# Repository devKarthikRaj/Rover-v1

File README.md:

# Rover-v1
<div align="center"></div><br>
<b>Rover v1 Documentation <br> 
Initial build completed on 21st January 2022.<br>
The inital build is a joystick controlled rover. <br>
Created for my own reference in the future and for any interested engineer wannabes (like myself) out there! <br> </b>

## Quick Reference
<b>Electrical</b> <br>
<i>Eagle PCBs</i> <br>
[Power Distribution Board](https://github.com/devKarthikRaj/Rover-v1/tree/master/Electrical/PCBs/Power%20Distribution%20Board/PDB%20v0) <br>
[Motor Driver](https://github.com/devKarthikRaj/Rover-v1/tree/master/Electrical/PCBs/Not%20in%20Use/Motor%20Driver/Rover%20MDrv%20v1) <br>
[Motor Controller](https://github.com/devKarthikRaj/Rover-v1/tree/master/Electrical/PCBs/Motor%20Controller/MCon%20v1) <br>
[Remote Control](https://github.com/devKarthikRaj/Rover-v1/tree/master/Electrical/PCBs/Remote%20Control/Rover%20Bt%20Remote) <br>

<i>Arduino Header Files</i> <br>
[Rover v1 Pin Configuration Header](https://github.com/devKarthikRaj/Rover-v1/tree/master/Electrical/Firmware/Arduino%20Libraries/roverV1) <br>

<i>Arduino Firmware</i> <br>
[Low Level Controller](https://github.com/devKarthikRaj/Rover-v1/tree/master/Electrical/Firmware/Low_Level_Controller_FW) <br>
[Motor Controller](https://github.com/devKarthikRaj/Rover-v1/tree/master/Electrical/Firmware/Motor_Controller_FW) <br>
[Remote Control](https://github.com/devKarthikRaj/Rover-v1/tree/master/Electrical/Firmware/Remote_Control_FW) <br>

<i>Overall Electrical System</i> <br>
[Block Diagram](https://github.com/devKarthikRaj/Rover-v1/blob/master/Electrical/Overall%20Electrical%20System/Overall%20Block%20Diagram/Overall%20Block%20Diagram.png) <br>
[Eagle Schematic](https://github.com/devKarthikRaj/Rover-v1/blob/master/Electrical/Overall%20Electrical%20System/Overall%20Schematic/Rover%20Overalls/Rover%20v1%20Overall.sch) <br>

<b>Mechanical</b> <br>
[Motor Mount Fusion 360 File](https://github.com/devKarthikRaj/Rover-v1/blob/master/Mechanical/Not%20in%20Use/Motor%20Mount%20v1.f3d) <br>
[Motor Mount GrabCAD](https://grabcad.com/library/gearbox-dc-motor-mount-1)<br>

___

# How it all came together
Warning - This is a long read! <br>

## I had been wanting to build something like this for quite a while now.  
I thought this would be easy and wouldn't take that long. Boy, was I wrong! Nevertheless, I had loads of fun doing this. Especially when everything worked! <br>

## A rocky start...
Kicked off the project by designing the mechanical aspect of the rover in Fusion 360 CAD. Initially decided to use those low cost yellow DC gear motors. YEAH I KNOW RIGHT, these motors are a pain to use just because they don't come with a mount, its not easy to mount these motors to ANYTHING! <br><br>
<div align="center"></div> <br>

So, I went on to CAD out a mount for these motors. <br>
<div align="center"></div> <br>

Eventually, I got the motor mounts 3D printed and assembled them. Functionality wise, these mounts were pretty good. Structurally, the screw holders at the side were too thin and broke off if stressed too much; but hey, the mounts got the job done... I'll let that pass! <br>
<div align="center">

</div> <br>
<div align="center"></div> <br>  
You can find these mounts on <a href="https://grabcad.com/library/gearbox-dc-motor-mount-1">GrabCAD</a> if you need the files. Feel free to use it. Give it a like too, that'll make my day! <br>

Motor mounts done. Need to mount them to something right? Its time to design the robot base. Came up with a race car/skateboard like shape for the base. <br>
<div align="center"></div> <br>

I laser cut the base and attached the motor mounts with the motor to the base. The chassis looked real good. <br> 
<div align="center"></div> <br>

I managed to complete only half the chassis though. Around this time, I graduated from school and lost access to all those wonderful machines (laser cutters, 3D printers, drills and stuff). Gone with the wind! There are 3D printing shops out there that offer low cost small scale printing for hobbyists like me! The problem was with finding a laser cutting shop or even a CNC shop for that matter - every place was expensive and only accepted large scale orders. Not hobbyist friendly. With a heavy heart... I discarded my beautiful half cooked chassis and took a break from the mechanical aspect. <br>

## A fresh start...
I started on the electrical aspect instead. My goal was to finish the electrical aspect first and then design the mechanical aspect accordingly to fit all the PCBs. Started out with the power circuit. 18650 Li-Ion batteries were my go to choice. Why? Surprisingly, 18650 Li-Ion batteries turned out to be cheaper than Li-Po batteries. Plus, Li-Ion is better than Li-Po as it has a higher power density... More juice in a smaller form factor! Next, I knew I'd need to step down the battery voltage to two different voltages. 5V for the digital circuitry and 6V to 12V for the motors. This is where the project kind of stagnated for a while. I really wanted to design a SMD PCB for the power circuit. THT PMICs were outdated and dissipated too much power which essentially means that the chip gets really HOT. Hot ain't good. SMD it is! THT is a no go! I designed 3 to 4 SMD power PCBs and got them manufactured. Next came the soldering, this is were I ran into a wall. Struggled with SMD soldering. Especially the IC chips. Those things are evil. This took too much of my time. Flushed that down the drain as well! Did some cheating here, I decided to buy pre-made power regulator boards. One for each voltage I required. They worked flawlessly! I'll definitely return to SMD and SMD soldering soon, maybe with a reflow hot plate, but not for this project! <br>

Next comes the motor circuitry. Started by designing a motor driver using the L298N H-bridge motor driver IC chip. It worked on the first try! I got lucky I guess! I wanted to step things up a notch. So, I went on to design a motor controller PCB. Basically, a motor driver circuit accompanied by a microcontroller (MCU). The MCU enables other PCBs to communicate with the motor controller through SPI. The MCU basically makes the motor controller "smart". It now has a brain. 
<div align="center"> </div> <br><br> 

The motor controller can be hooked up with an emergency stop (eStop) switch too.
<div align="center"></div> <br> 
 
Motor controller in action:
<div align="center"></div> <br>

### An emotional rollercoaster...
Sad story incoming. On top of all that, I also added a provision for an accelerometer module to be interfaced with the MCU on the motor controller board. The whole point of the accelerometer was to make the robot go straight. Supplying the exact same voltage to two motors of the same model will not make them spin at exactly the same rate. One motor "might" be slightly faster than the other. Every motor is different. The robot won't move in a straight line unless I have feedback control to ensure that the robot moves in a straight line. Instead of using a motor fitted with an encoder to measure distance travelled by each wheel and then feedback to the MCU to adjust accordingly, I thought of trying something new. Using an accelerometer module to measure the distance. This turned out to be extremely challenging. To obtain distance from an accelerometer, you'd have to double integrate and the result is extremely inaccurate. Espcially over time, the error increases exponentially. The accelerometer did work though. For the record, I managed to get data out of the accelerometer:
<div align="center"></div> <br> 
Since that was a dead end, I dropped the accelerometer and tried using a compass magnetometer module to measure heading. Then, orientate the robot accordingly if the robot is off course. Long story short, this turned out to be difficult as well. The compass outputs x,y,z axis values. With this I know which direction the robot is facing. However, translating this data into PWM commands to supply to the motor controller to adjust the heading of the robot proved to be challenging. I wanted to use PID control for this but I couldn't establish a link between the INPUT (magnetometer's x,y,z values) and the OUTPUT (PWM motor values). Ended up scrapping that idea as well. *Cry cry* <br> 
Pro tip - Best way to measure distance travelled by a robot is to use motors with encoders! I think I've learnt a very good lesson here :) <br> <br>

The only PCB left to work on was the PCB to distribute the two voltages to their own power rails so that the other PCBs can tap from these rails. Very simple. No complex circuits involved. This didn't take too long to get done.

## So done with the mechanical aspect...
Since I lost access to all those machines in school post graduation, I decided to get Tamiya parts. Tamiya has a lot of versatile products and its low cost, just what I was looking for. I also decided to use stronger motors. From a previous partially working obstacle sensor robot project, I knew that those yellow gear motors can't carry heavy loads. This robot was leaning on the heavier side. Especially with four 18650 batteries. So I bought some machifit gear motors, slightly more expensive than the yellow gear motors, but these machifit motors come with their own mount and nuts & bolts and can be hooked up to almost anything! How nice!  

Since the motor controller was an "overall" success and since I secured all the Tamiya mechanical parts from Japan and new motors from China, It was time to hook everything up. 
<div align="center"></div> <br>

## A hot mess...
Yes. I know the whole rover sounds like a hot mess (not literally... my PCBs are cool as cucumbers). So, here's the block diagram of the rover's electrical system. The big picture:

The so called "low level controller (LLC)" here acts as a middle man. The low level controller is just an Arduino Mega board. The LLC communicates with the remote control for the rover via Bluetooth and sends the data received from the Bluetooth remote to the motor controller via SPI. In the future, if I add sensors to this rover, the sensors will also interact with the low level controller. The low level controller will process the sensor data and send control signals to the motor controller accordingly. Having the LLC will hopefully allow me to upgrade this rover hassle free in the future!   

The assembly was smooth as butter. The entire electrical system was wired up and "WORKING" on my table. That's what I'm talking about! Robot on table:
<div align="center"></div> <br> 

Last but not least - the firmware for all the MCUs on the rover and the Bluetooth remote. Writing firmware is always fun. Even though I encountered half a million exceptions. I'm kidding. 
## Baby steps
The first time the rover moved...
<div align="center"></div> <br> 

## Rover gone mad
Bug filled code creating chaos...
<i>This was when I was still trying to control the robot using the accelerometer and magnetometer</i>
<div align="center"></div> <br> 

## Rover in action!
It works!
<div align="center"></div> <br>

Oh oh... I totally forgot about the remote control. It was still contained on a breadboard, running off my old Arduino Uno. Quickly made a THT PCB and got it manufactured and soldered. Took about a few hours to design the PCB in Eagle and 2 weeks for it to be delivered. Soldered it and boom! Done! One good thing that came about from designing so many failed PCBs - now I can whip up simple "WORKING" boards in a few hours... Yay!
<div align="center">

</div>
<div align="center"></div> <br>

The remote control needed a case! Luckily I saved some unused 3D printed acrylic mounts from a school project a few years ago. Zip tied the remote control PCB and stuck the 9V battery to the mount.
<div align="center"></div> <br>

Stick a fork in it people! We done!
<div align="center"></div>

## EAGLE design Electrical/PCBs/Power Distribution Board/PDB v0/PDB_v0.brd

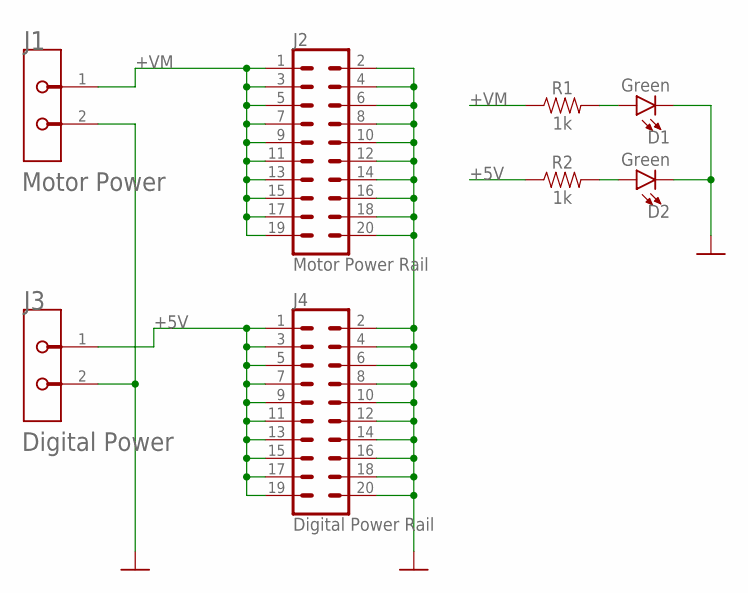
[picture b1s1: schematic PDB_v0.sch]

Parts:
D1, D2: Green; LED_3MM
J1: Motor Power; TE_282837-2_0
J2: Motor Power Rail; 2X10
J3: Digital Power; TE_282837-2_0
J4: Digital Power Rail; 2X10
R1, R2: 1k; AXIAL-0.3

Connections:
+5V: J3.1, J4.1, J4.3, J4.5, J4.7, J4.9, J4.11, J4.13, J4.15, J4.17, J4.19, R2.P$1 (1)
+VM: J1.1, J2.1, J2.3, J2.5, J2.7, J2.9, J2.11, J2.13, J2.15, J2.17, J2.19, R1.P$1 (1)
GND: D1.K (C), D2.K (C), J1.2, J2.2, J2.4, J2.6, J2.8, J2.10, J2.12, J2.14, J2.16, J2.18, J2.20, J3.2, J4.2, J4.4, J4.6, J4.8, J4.10, J4.12, J4.14, J4.16, J4.18, J4.20
unnamed: D1.A, R1.P$2 (2)
unnamed: D2.A, R2.P$2 (2)

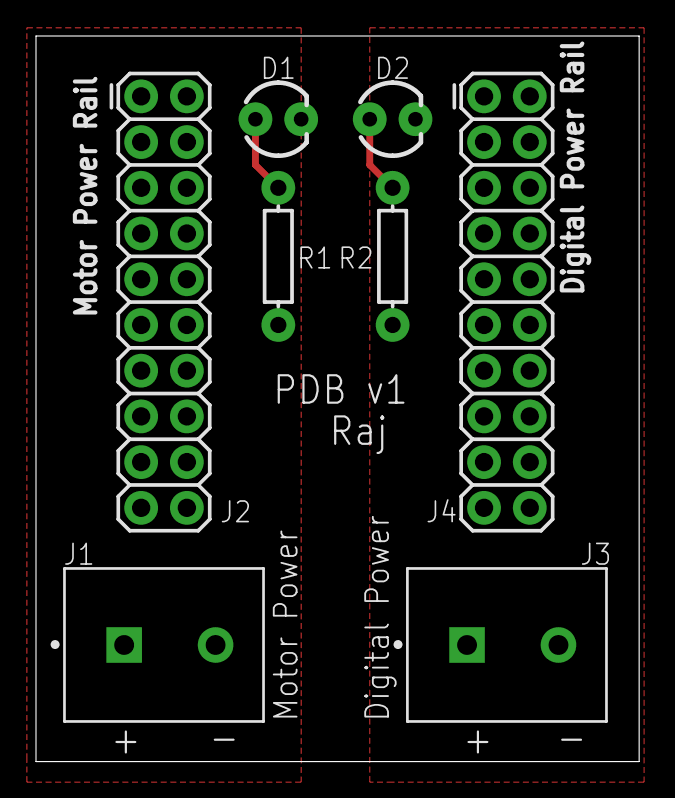
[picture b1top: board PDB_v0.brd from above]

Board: 2 copper layers, 33.5 x 40.3 mm, 8 parts (0 on the bottom side), 5 nets.

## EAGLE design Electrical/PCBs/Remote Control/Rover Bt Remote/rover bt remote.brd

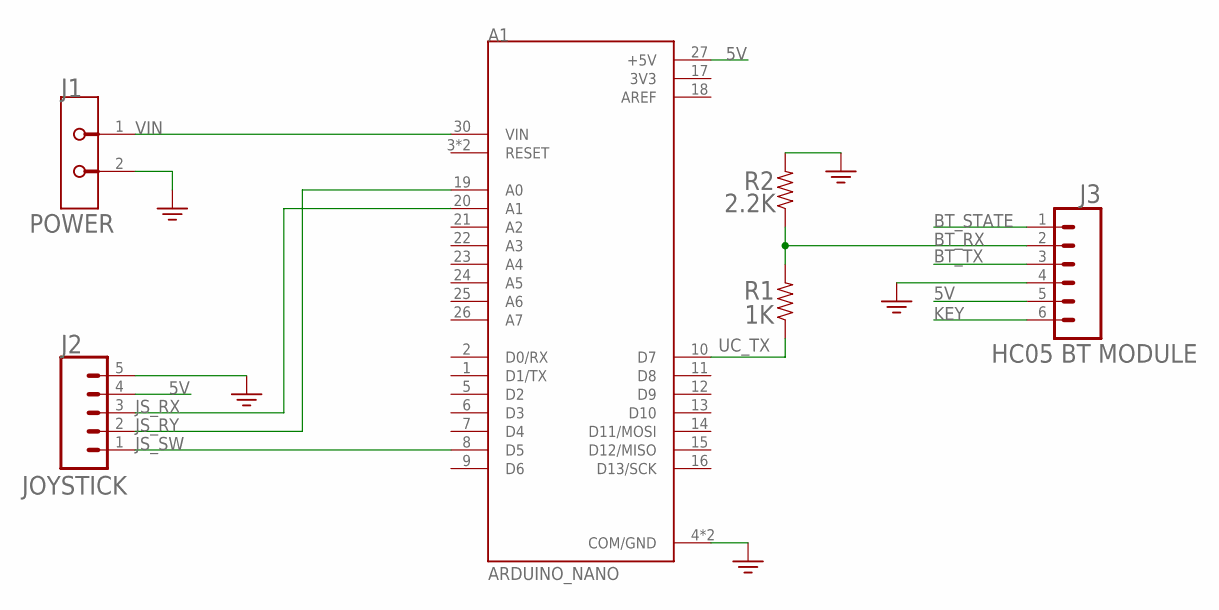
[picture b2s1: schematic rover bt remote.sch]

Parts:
A1: ARDUINO_NANO; SHIELD_ARDUINO_NANO
J1: POWER; TE_282837-2_0
J2: JOYSTICK; 1X05
J3: HC05 BT MODULE; 1X06
R1: 1K; AXIAL-0.3
R2: 2.2K; AXIAL-0.3

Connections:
3V3: A1.17 (3V3)
5V: A1.27 (+5V), J2.4, J3.5
AREF: A1.18 (AREF)
BT_RX: J3.2, R1.P$2 (2), R2.P$1 (1)
BT_STATE: J3.1
BT_TX: J3.3
GND: A1.4 (COM/GND), A1.29 (COM/GND), J1.2, J2.5, J3.4, R2.P$2 (2)
JS_RX: A1.20 (A1), J2.3
JS_RY: A1.19 (A0), J2.2
JS_SW: A1.8 (D5), J2.1
KEY: J3.6
UC_TX: A1.10 (D7), R1.P$1 (1)
VIN: A1.30 (VIN), J1.1

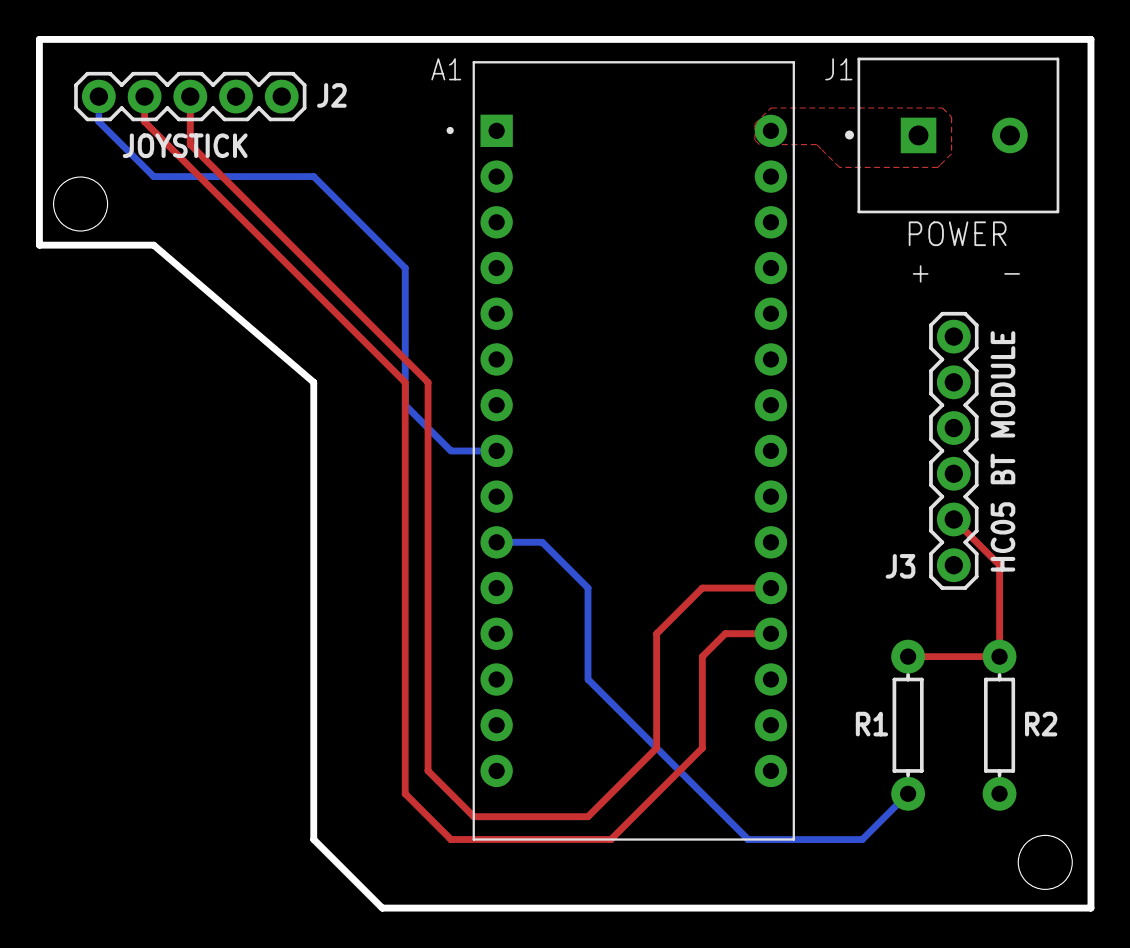
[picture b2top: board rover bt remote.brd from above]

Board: 2 copper layers, 58.4 x 48.3 mm, 6 parts (0 on the bottom side), 8 nets.

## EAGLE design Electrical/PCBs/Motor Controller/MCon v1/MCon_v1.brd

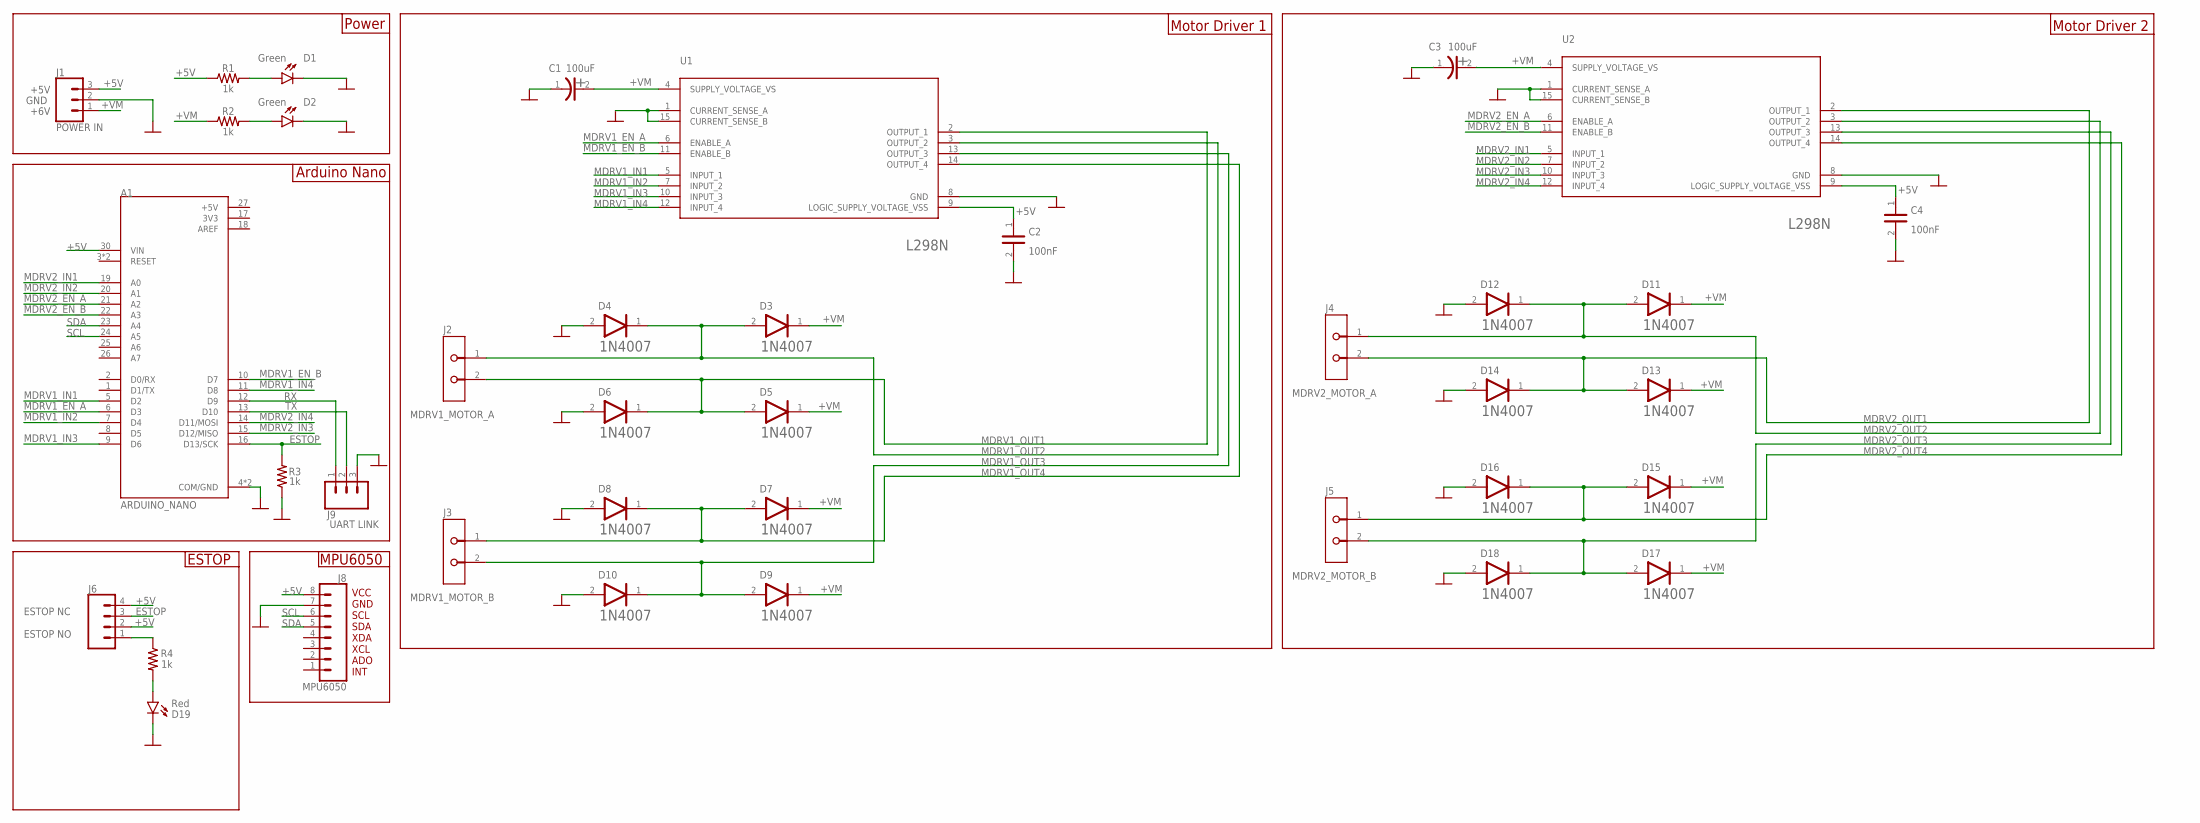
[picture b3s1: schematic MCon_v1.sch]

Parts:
A1: ARDUINO_NANO; SHIELD_ARDUINO_NANO
C1, C3: 100uF; PANASONIC_EEU-FR1C101_0
C2, C4: 100nF; AVX_CK05BX104K_0
D1, D2: Green; LED_3MM
D3, D4, D5, D6, D7, D8, D9, D10, D11, D12, D13, D14, D15, D16, D17, D18: DIOTEC_1N4007DIOTEC_1N4007_0_0; DIOTEC_1N4007_0
D19: Red; LED_3MM
J1: POWER IN; 1X03
J2: MDRV1_MOTOR_A; TE_282837-2_0
J3: MDRV1_MOTOR_B; TE_282837-2_0
J4: MDRV2_MOTOR_A; TE_282837-2_0
J5: MDRV2_MOTOR_B; TE_282837-2_0
J6: CONN_04PTH; 1X04
J8: MPU6050; 1X08
J9: UART LINK; 1X03
R1, R2, R3, R4: 1k; AXIAL-0.3
U1, U2: STMICROELECTRONICS_L298NSTMICROELECTRONICS_L298N_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; STMICROELECTRONICS_L298N_0

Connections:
3V3: A1.17 (3V3)
+5V: A1.27 (+5V), A1.30 (VIN), C2.1, C4.1, J1.3, J6.2, J6.4, J8.8, R1.P$1 (1), U1.9 (LOGIC_SUPPLY_VOLTAGE_VSS), U2.9 (LOGIC_SUPPLY_VOLTAGE_VSS)
+VM: C1.2 (ANODE), C3.2 (ANODE), D3.1 (CATHODE), D5.1 (CATHODE), D7.1 (CATHODE), D9.1 (CATHODE), D11.1 (CATHODE), D13.1 (CATHODE), D15.1 (CATHODE), D17.1 (CATHODE), J1.1, R2.P$1 (1), U1.4 (SUPPLY_VOLTAGE_VS), U2.4 (SUPPLY_VOLTAGE_VS)
AREF: A1.18 (AREF)
ESTOP: A1.16 (D13/SCK), J6.3, R3.P$2 (2)
GND: A1.4 (COM/GND), A1.29 (COM/GND), C1.1 (CATHODE), C2.2, C3.1 (CATHODE), C4.2, D1.K (C), D2.K (C), D4.2 (ANODE), D6.2 (ANODE), D8.2 (ANODE), D10.2 (ANODE), D12.2 (ANODE), D14.2 (ANODE), D16.2 (ANODE), D18.2 (ANODE), D19.K (C), J1.2, J8.7, J9.3, R3.P$1 (1), U1.1 (CURRENT_SENSE_A), U1.8 (GND), U1.15 (CURRENT_SENSE_B), U2.1 (CURRENT_SENSE_A), U2.8 (GND), U2.15 (CURRENT_SENSE_B)
MDRV1_EN_A: A1.6 (D3), U1.6 (ENABLE_A)
MDRV1_EN_B: A1.10 (D7), U1.11 (ENABLE_B)
MDRV1_IN1: A1.5 (D2), U1.5 (INPUT_1)
MDRV1_IN2: A1.7 (D4), U1.7 (INPUT_2)
MDRV1_IN3: A1.9 (D6), U1.10 (INPUT_3)
MDRV1_IN4: A1.11 (D8), U1.12 (INPUT_4)
MDRV1_OUT1: D5.2 (ANODE), D6.1 (CATHODE), J2.2, U1.2 (OUTPUT_1)
MDRV1_OUT2: D3.2 (ANODE), D4.1 (CATHODE), J2.1, U1.3 (OUTPUT_2)
MDRV1_OUT3: D9.2 (ANODE), D10.1 (CATHODE), J3.2, U1.13 (OUTPUT_3)
MDRV1_OUT4: D7.2 (ANODE), D8.1 (CATHODE), J3.1, U1.14 (OUTPUT_4)
MDRV2_EN_A: A1.21 (A2), U2.6 (ENABLE_A)
MDRV2_EN_B: A1.22 (A3), U2.11 (ENABLE_B)
MDRV2_IN1: A1.19 (A0), U2.5 (INPUT_1)
MDRV2_IN2: A1.20 (A1), U2.7 (INPUT_2)
MDRV2_IN3: A1.15 (D12/MISO), U2.10 (INPUT_3)
MDRV2_IN4: A1.14 (D11/MOSI), U2.12 (INPUT_4)
MDRV2_OUT1: D13.2 (ANODE), D14.1 (CATHODE), J4.2, U2.2 (OUTPUT_1)
MDRV2_OUT2: D11.2 (ANODE), D12.1 (CATHODE), J4.1, U2.3 (OUTPUT_2)
MDRV2_OUT3: D17.2 (ANODE), D18.1 (CATHODE), J5.2, U2.13 (OUTPUT_3)
MDRV2_OUT4: D15.2 (ANODE), D16.1 (CATHODE), J5.1, U2.14 (OUTPUT_4)
unnamed: D1.A, R1.P$2 (2)
unnamed: D2.A, R2.P$2 (2)
unnamed: J6.1, R4.P$1 (1)
unnamed: D19.A, R4.P$2 (2)
RX: A1.12 (D9), J9.1
SCL: A1.24 (A5), J8.6
SDA: A1.23 (A4), J8.5
TX: A1.13 (D10), J9.2

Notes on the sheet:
+5V
GND
+6V
Power
Motor Driver 1
Motor Driver 2
ESTOP
VCC GND SCL SDA XDA XCL ADO INT
MPU6050
Arduino Nano
ESTOP NC ESTOP NO

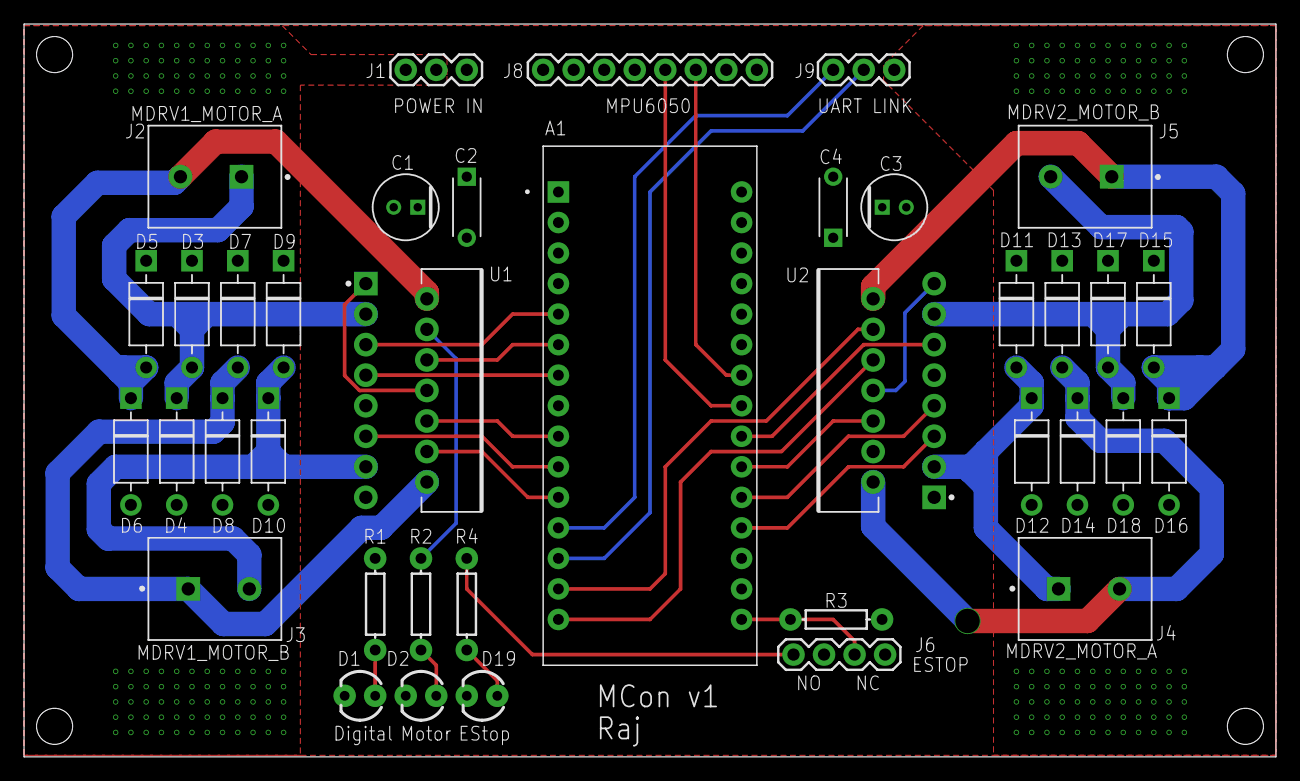
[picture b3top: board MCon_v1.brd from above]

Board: 2 copper layers, 104.1 x 61.0 mm, 38 parts (0 on the bottom side), 32 nets.

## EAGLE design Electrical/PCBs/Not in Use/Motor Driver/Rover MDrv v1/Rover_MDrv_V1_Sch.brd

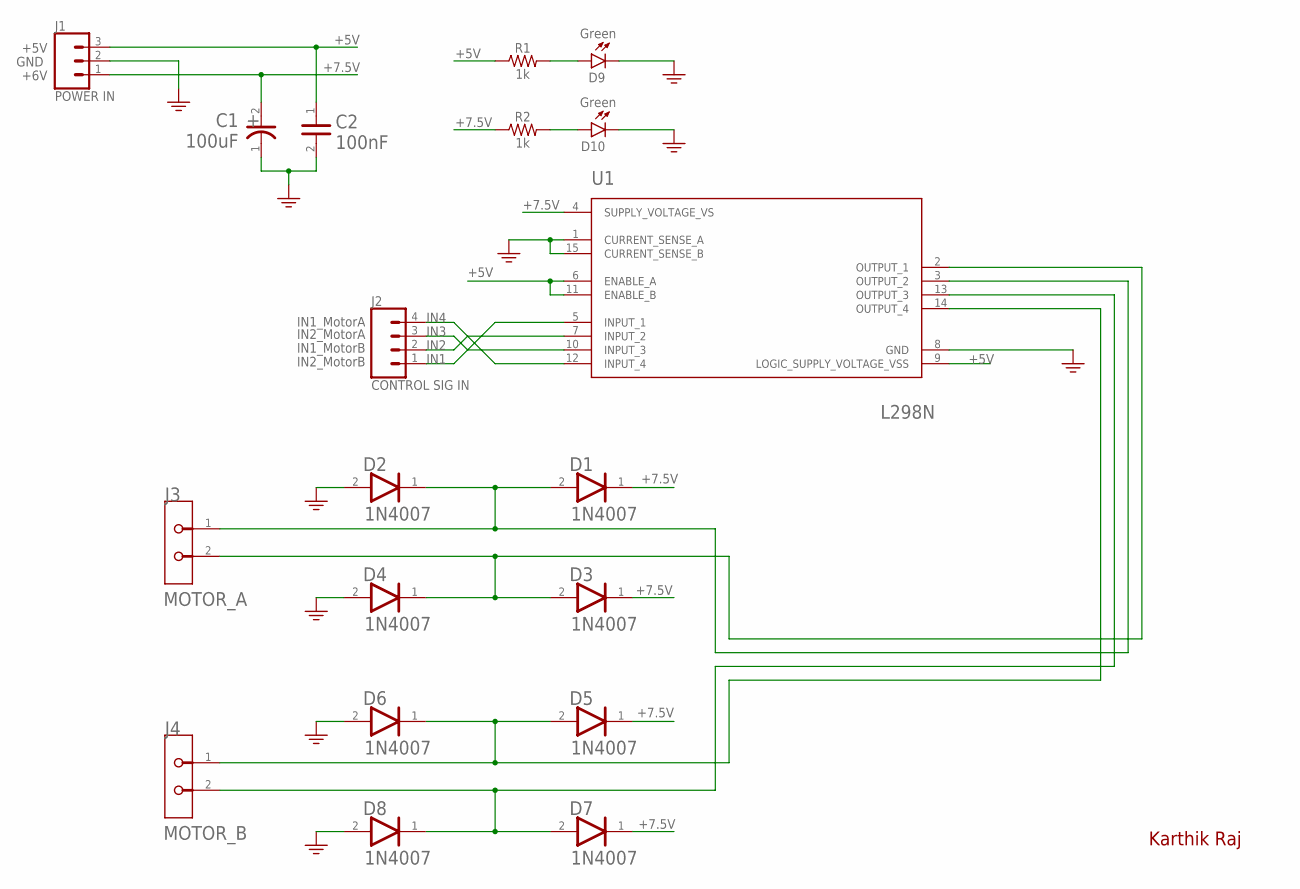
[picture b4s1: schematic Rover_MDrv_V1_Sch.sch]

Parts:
C1: 100uF; PANASONIC_EEU-FR1C101_0
C2: 100nF; AVX_CK05BX104K_0
D1, D2, D3, D4, D5, D6, D7, D8: DIOTEC_1N4007DIOTEC_1N4007_0_0; DIOTEC_1N4007_0
D9, D10: Green; LED_3MM
J1: POWER IN; 1X03
J2: CONTROL SIG IN; 1X04
J3: MOTOR_A; TE_282837-2_0
J4: MOTOR_B; TE_282837-2_0
R1, R2: 1k; AXIAL-0.3
U1: STMICROELECTRONICS_L298NSTMICROELECTRONICS_L298N_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; STMICROELECTRONICS_L298N_0

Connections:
+5V: C2.1, J1.3, R1.P$1 (1), U1.6 (ENABLE_A), U1.9 (LOGIC_SUPPLY_VOLTAGE_VSS), U1.11 (ENABLE_B)
+7.5V: C1.2 (ANODE), D1.1 (CATHODE), D3.1 (CATHODE), D5.1 (CATHODE), D7.1 (CATHODE), J1.1, R2.P$1 (1), U1.4 (SUPPLY_VOLTAGE_VS)
GND: C1.1 (CATHODE), C2.2, D2.2 (ANODE), D4.2 (ANODE), D6.2 (ANODE), D8.2 (ANODE), D9.K (C), D10.K (C), J1.2, U1.1 (CURRENT_SENSE_A), U1.8 (GND), U1.15 (CURRENT_SENSE_B)
IN1: J2.1, U1.5 (INPUT_1)
IN2: J2.2, U1.7 (INPUT_2)
IN3: J2.3, U1.10 (INPUT_3)
IN4: J2.4, U1.12 (INPUT_4)
unnamed: D9.A, R1.P$2 (2)
unnamed: D10.A, R2.P$2 (2)
OUT1: D3.2 (ANODE), D4.1 (CATHODE), J3.2, U1.2 (OUTPUT_1)
OUT2: D1.2 (ANODE), D2.1 (CATHODE), J3.1, U1.3 (OUTPUT_2)
OUT3: D7.2 (ANODE), D8.1 (CATHODE), J4.2, U1.13 (OUTPUT_3)
OUT4: D5.2 (ANODE), D6.1 (CATHODE), J4.1, U1.14 (OUTPUT_4)

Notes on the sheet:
+5V
GND
+6V
IN1_MotorA
IN2_MotorA
IN1_MotorB
IN2_MotorB
Karthik Raj

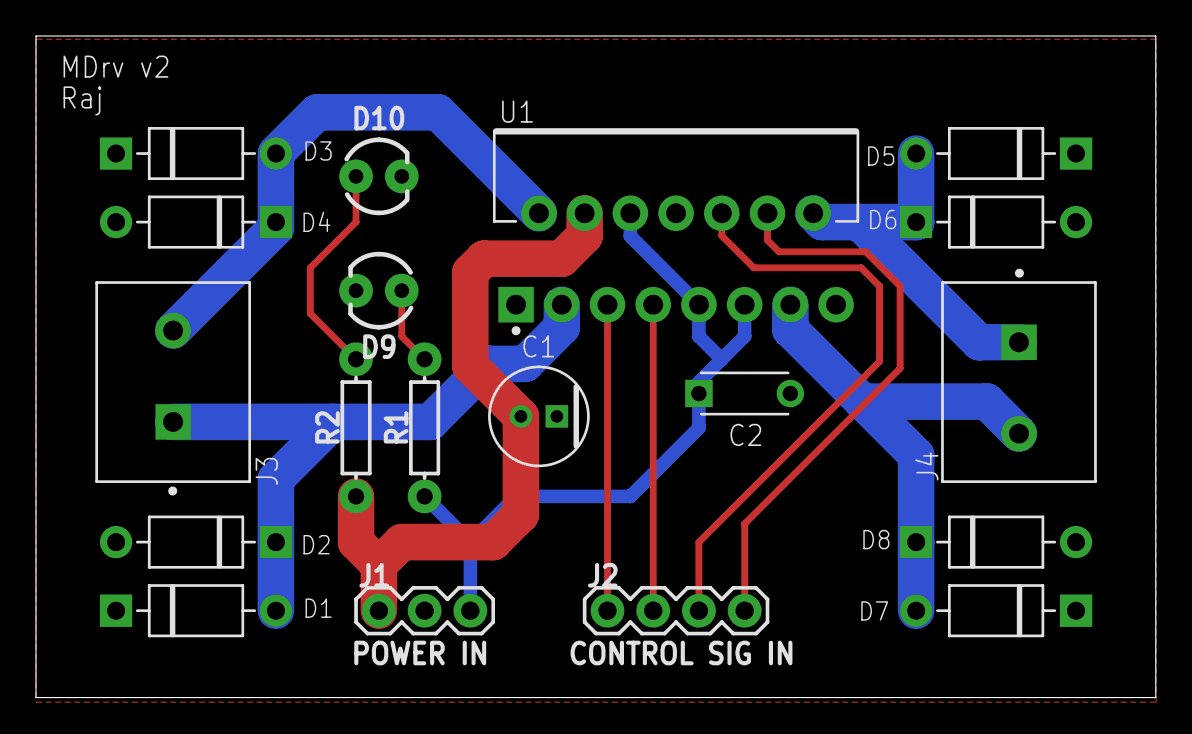
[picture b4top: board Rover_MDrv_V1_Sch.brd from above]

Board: 2 copper layers, 62.2 x 36.8 mm, 19 parts (0 on the bottom side), 13 nets.

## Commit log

2022-01-09 Added in overalls and firmware header comments
2022-01-26 Bug fixes and added pictures
2022-01-27 Updated readme and added pics
2022-01-27 Renamed folders
2022-01-27 Updated readme and converted mp4 files to gifs
2022-01-27 Updated media folder

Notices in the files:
parts and their libraries:
SparkFun-LED: Licensing: Creative Commons ShareAlike 4.0 International - https://creativecommons.org/licenses/by-sa/4.0
